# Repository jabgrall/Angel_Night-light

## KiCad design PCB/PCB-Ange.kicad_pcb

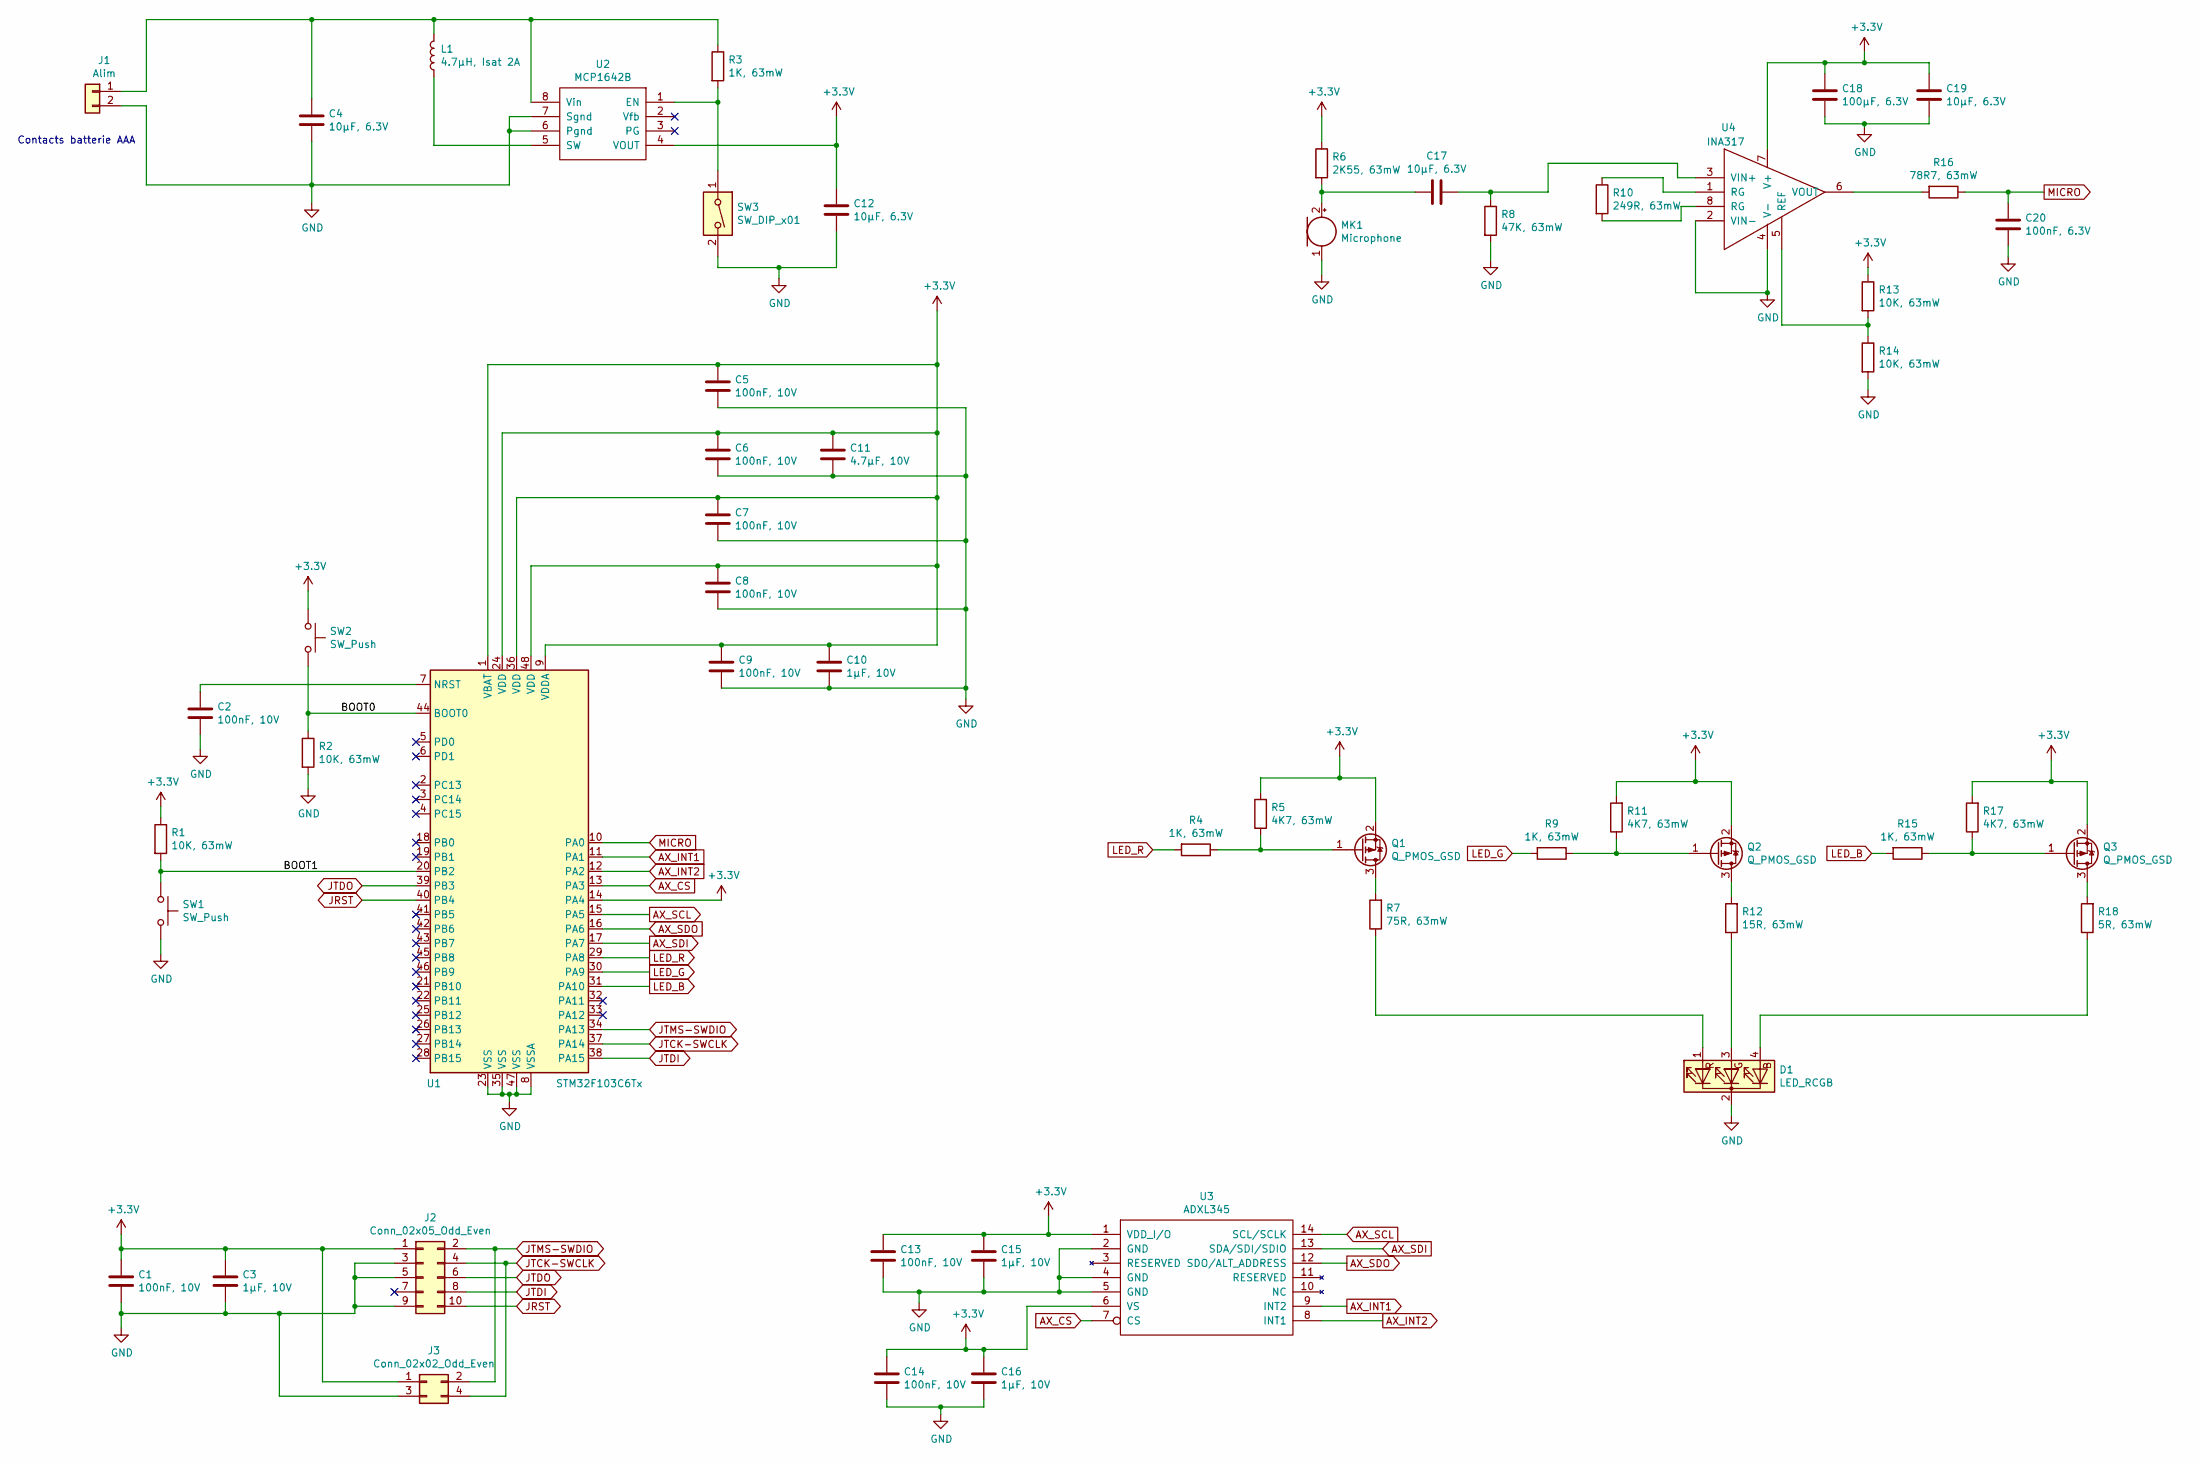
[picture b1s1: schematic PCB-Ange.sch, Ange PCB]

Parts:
C1, C2, C5, C6, C7, C8, C9, C13, C14: 100nF, 10V; R_0603_1608Metric_Pad1.05x0.95mm_HandSolder
C3, C10, C15, C16: 1µF, 10V; R_0603_1608Metric_Pad1.05x0.95mm_HandSolder
C4, C12, C17, C19: 10µF, 6.3V; R_0603_1608Metric_Pad1.05x0.95mm_HandSolder
C11: 4.7µF, 10V; R_0603_1608Metric_Pad1.05x0.95mm_HandSolder
C18: 100µF, 6.3V; R_1210_3225Metric_Pad1.42x2.65mm_HandSolder
C20: 100nF, 6.3V; R_0603_1608Metric_Pad1.05x0.95mm_HandSolder
D1: LED_RCGB; LED_D5.0mm-4_RGB
J1: Alim; Keystone_SMD_5230_AAA
J2: Conn_02x05_Odd_Even; PinHeader_2x05_P1.27mm_Vertical_SMD
J3: Conn_02x02_Odd_Even; PinHeader_2x02_P1.27mm_Vertical_SMD
L1: 4.7µH, Isat 2A; L_Bourns-SRN4018
MK1: Microphone; micro_4mm
Q1, Q2, Q3: Q_PMOS_GSD; SOT-723
R1, R2, R13, R14: 10K, 63mW; R_0603_1608Metric_Pad1.05x0.95mm_HandSolder
R3, R4, R9, R15: 1K, 63mW; R_0603_1608Metric_Pad1.05x0.95mm_HandSolder
R5, R11, R17: 4K7, 63mW; R_0603_1608Metric_Pad1.05x0.95mm_HandSolder
R6: 2K55, 63mW; R_0603_1608Metric_Pad1.05x0.95mm_HandSolder
R7: 75R, 63mW; R_0603_1608Metric_Pad1.05x0.95mm_HandSolder
R8: 47K, 63mW; R_0603_1608Metric_Pad1.05x0.95mm_HandSolder
R10: 249R, 63mW; R_0603_1608Metric_Pad1.05x0.95mm_HandSolder
R12: 15R, 63mW; R_0603_1608Metric_Pad1.05x0.95mm_HandSolder
R16: 78R7, 63mW; R_0603_1608Metric_Pad1.05x0.95mm_HandSolder
R18: 5R, 63mW; R_0603_1608Metric_Pad1.05x0.95mm_HandSolder
SW1, SW2: SW_Push; SW_SPST_B3U-1000P-B
SW3: SW_DIP_x01; SW_DIP_SPSTx01_Slide_6.7x4.1mm_W8.61mm_P2.54mm_LowProfile
U1: STM32F103C6Tx; LQFP-48_7x7mm_P0.5mm
U2: MCP1642B; MSOP-8_3x3mm_P0.65mm
U3: ADXL345; LGA-14_3x5mm_P0.8mm_LayoutBorder1x6y
U4: INA317; VSSOP-8_3.0x3.0mm_P0.65mm

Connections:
+3V3: C1.1, C3.1, C5.1, C6.1, C7.1, C8.1, C9.1, C10.1, C11.1, C12.1, C13.1, C14.1, C15.1, C16.1, C18.1, C19.1, J2.1, J3.1, Q1.2 (S), Q2.2 (S), Q3.2 (S), R1.1, R5.2, R6.1, R11.2, R13.1, R17.2, SW2.1, U1.1 (VBAT), U1.9 (VDDA), U1.14 (PA4), U1.24 (VDD), U1.36 (VDD), U1.48 (VDD), U2.4 (VOUT), U3.1 (VDD_I/O), U3.6 (VS), U4.7 (V+)
/BOOT0: R2.1, SW2.2, U1.44 (BOOT0)
/BOOT1: R1.2, SW1.1, U1.20 (PB2)
AX_CS: U1.13 (PA3), U3.7 (CS)
AX_INT1: U1.11 (PA1), U3.9 (INT2)
AX_INT2: U1.12 (PA2), U3.8 (INT1)
AX_SCL: U1.15 (PA5), U3.14 (SCL/SCLK)
AX_SDI: U1.17 (PA7), U3.13 (SDA/SDI/SDIO)
AX_SDO: U1.16 (PA6), U3.12 (SDO/ALT_ADDRESS)
GND: C1.2, C2.2, C3.2, C4.2, C5.2, C6.2, C7.2, C8.2, C9.2, C10.2, C11.2, C12.2, C13.2, C14.2, C15.2, C16.2, C18.2, C19.2, C20.2, D1.2 (K), J1.2, J2.3, J2.5, J2.9, J3.3, MK1.1 (-), R2.2, R8.2, R14.2, SW1.2, SW3.2, U1.8 (VSSA), U1.23 (VSS), U1.35 (VSS), U1.47 (VSS), U2.6 (Pgnd), U2.7 (Sgnd), U3.2 (GND), U3.4 (GND), U3.5 (GND), U4.2 (VIN-), U4.4 (V-)
JRST: J2.10, U1.40 (PB4)
JTCK-SWCLK: J2.4, J3.4, U1.37 (PA14)
JTDI: J2.8, U1.38 (PA15)
JTDO: J2.6, U1.39 (PB3)
JTMS-SWDIO: J2.2, J3.2, U1.34 (PA13)
LED_B: R15.2, U1.31 (PA10)
LED_G: R9.2, U1.30 (PA9)
LED_R: R4.2, U1.29 (PA8)
MICRO: C20.1, R16.1, U1.10 (PA0)
unnamed: C2.1, U1.7 (NRST)
unnamed: C4.1, J1.1, L1.2, R3.1, U2.8 (Vin)
unnamed: C17.1, R8.1, U4.3 (VIN+)
unnamed: C17.2, MK1.2 (+), R6.2
unnamed: D1.1 (RA), R7.1
unnamed: D1.3 (GA), R12.1
unnamed: D1.4 (BA), R18.1
unnamed: L1.1, U2.5 (SW)
unnamed: Q1.1 (G), R4.1, R5.1
unnamed: Q1.3 (D), R7.2
unnamed: Q2.1 (G), R9.1, R11.1
unnamed: Q2.3 (D), R12.2
unnamed: Q3.1 (G), R15.1, R17.1
unnamed: Q3.3 (D), R18.2
unnamed: R3.2, SW3.1, U2.1 (EN)
unnamed: R10.1, U4.1 (RG)
unnamed: R10.2, U4.8 (RG)
unnamed: R13.2, R14.1, U4.5 (REF)
unnamed: R16.2, U4.6 (VOUT)

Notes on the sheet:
Contacts batterie AAA

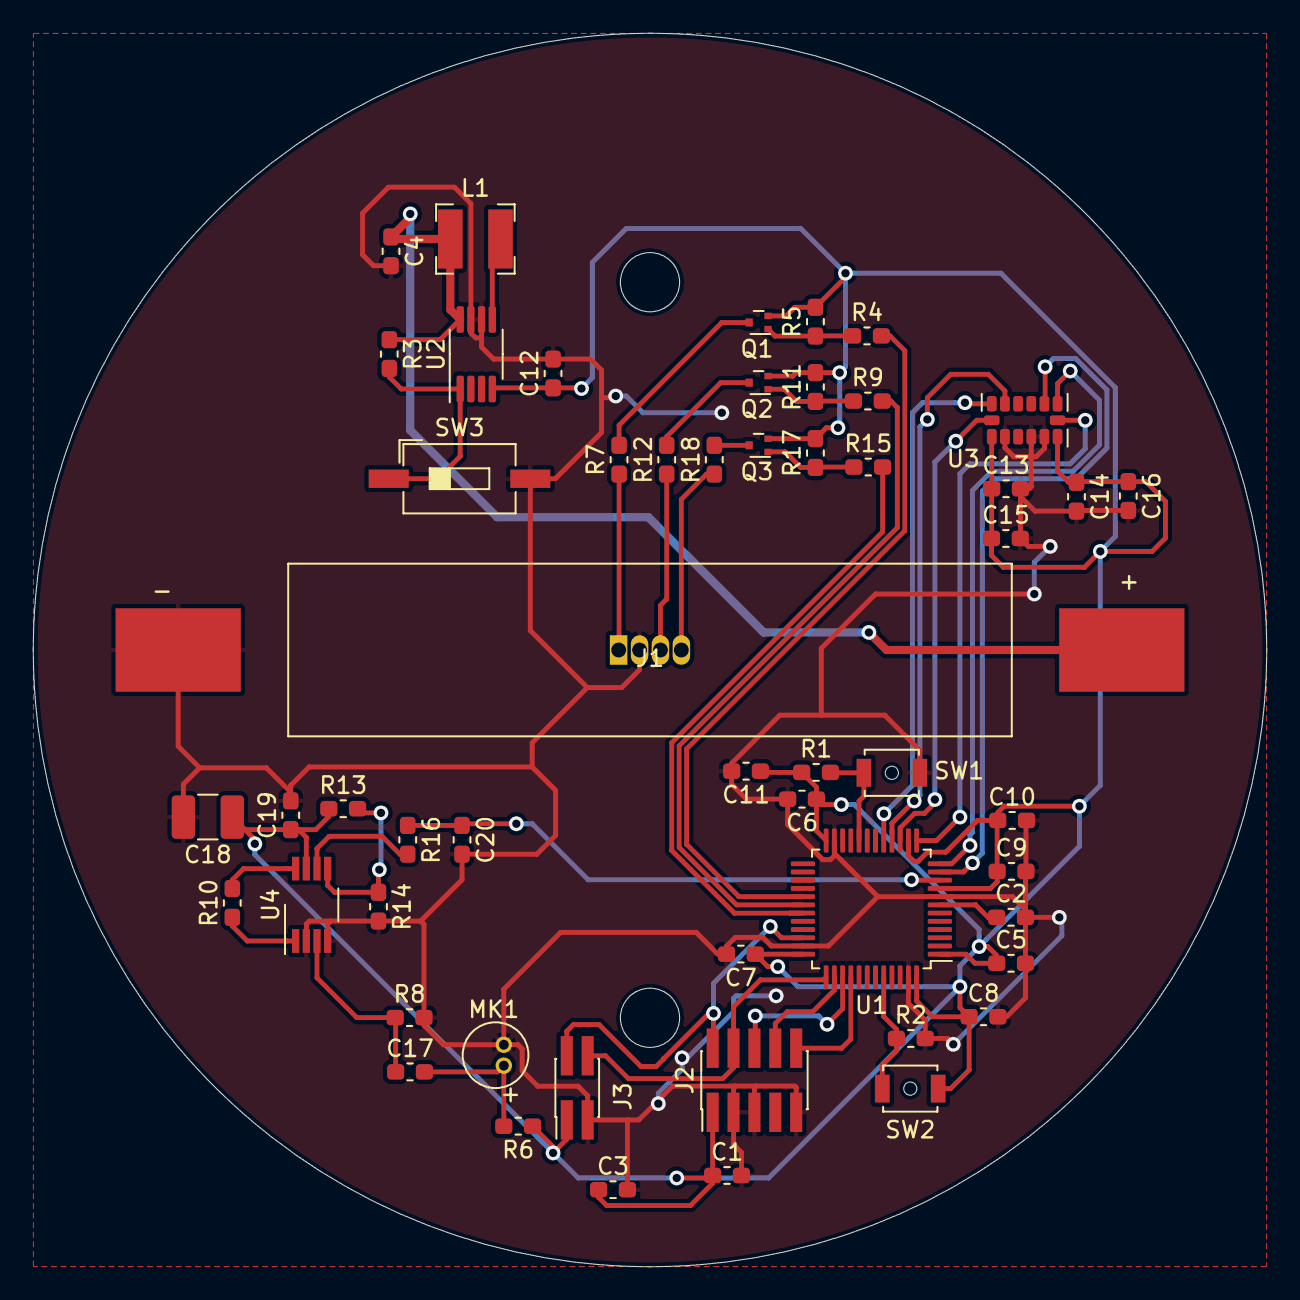
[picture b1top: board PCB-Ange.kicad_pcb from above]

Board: 2 copper layers, 75.0 x 75.0 mm, 54 parts (1 on the bottom side), 38 nets.

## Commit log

2021-09-29 Sauvegarde du soir 29/09/2021
2021-09-30 maj 230/09/21 7h10
2021-09-30 Sauvegarde du 30/09/2021 17:37
2021-10-01 Sauvegarde 01/10/2021 16h10
2021-10-05 Sauvegarde 05/10/2021 17h25
2021-10-19 Sauvegarde du 19/10/21 7h44
2021-11-12 Sauvegarde du 12/11/21, 10:17
2022-03-18 Update du 18 mars à 17:33
2022-06-29 update du 29/06/22 à 21:17
2022-08-24 Update du 24/08/22 à 21:34
2022-08-24 Update du 24/08/22 a 21:46
2022-08-24 Update du 24/08/22 à 22:17
2022-08-24 Update du 24/08/22 à 22:30
2022-08-24 Update du 24/08/22 à 23:34
2022-08-24 Update du 24/08/22 à 23:35
2022-08-25 Update du 25/08/22 à 07:56
2022-08-26 Update du 26/08/22 à 7:53
2022-08-29 Update du 29/08/22 à 7:52
2022-09-20 Update du 20/09/2022 à 7h47
2022-10-18 Update du 18/10/2022 à 07:31.
2022-10-25 Update du 25/10/22 à 07:42.
2022-10-26 Update du 26/10/22 à 07:33.
2022-11-09 Update du 9/11/22 à 07:48
